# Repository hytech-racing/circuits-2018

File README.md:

# 2018 Circuits

## Getting Started with this git repository
1. Download and install [Github Desktop](https://desktop.github.com/) (basic) or [git](https://git-scm.com/book/en/v2/Getting-Started-Installing-Git) (advanced)
    * If you are using Github Desktop for the first time, be sure to read the [User Guide](https://help.github.com/desktop/guides/)
    * If you are using git for the first time, you should start off by reading a tutorial. There are many available online:
        * [Atlassian Git Tutorial](https://www.atlassian.com/git/tutorials/)
        * [Pro Git book](https://git-scm.com/book/en/v2)
    * You may want to keep a copy of [Github's Git Cheat Sheet](https://services.github.com/kit/downloads/github-git-cheat-sheet.pdf) as a reference
2. Create a Github account if you don't already have one
3. Talk to your subteam lead to be added to your respective team on the Github organization
4. Clone this repository to your computer
    * SSH: git@github.com:hytech-racing/circuits-2018.git
    * HTTPS: https://github.com/hytech-racing/circuits-2018.git

## Getting Started with EAGLE
1. Download and install [EAGLE](https://www.autodesk.com/products/eagle/overview)
2. Get the free [Educational License](https://www.autodesk.com/education/free-software/eagle) (a .edu email address is required)

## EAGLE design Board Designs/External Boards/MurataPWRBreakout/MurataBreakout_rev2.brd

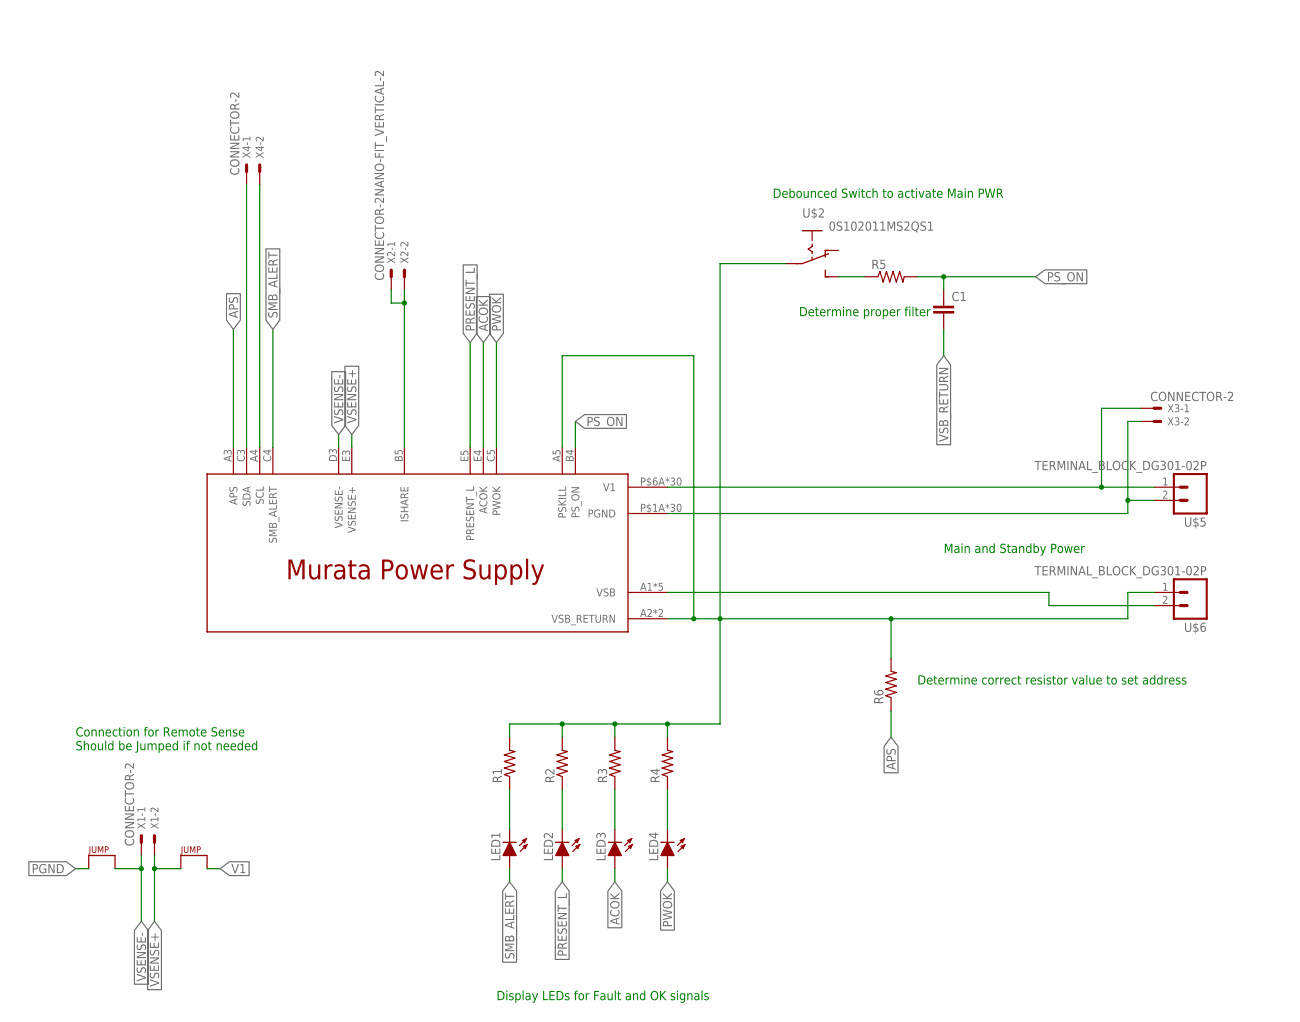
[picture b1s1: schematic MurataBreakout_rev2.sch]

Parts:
C1: CAP0805; 0805
LED1, LED2, LED3, LED4: LED-0805; LED-805
R1, R2, R3, R4, R5, R6: RESISTOR0805-RES; 0805
U$1: MURATA_POWER_SUPPLY; MURATA_POWER_SUPPLY_CONNECTOR
U$2: 0S102011MS2QS1
U$3, U$4: JUMPER.1; 1X02
U$5, U$6: TERMINAL_BLOCK_DG301-02P; DG301-02P
X1, X3, X4: CONNECTOR-2; MINIFIT_5566-2
X2: CONNECTOR-2NANO-FIT_VERTICAL-2; NANO-FIT_VERTICAL-2

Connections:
ACOK: LED3.A, U$1.E4 (ACOK)
APS: R6.1, U$1.A3 (APS)
unnamed: LED4.C, R4.1
unnamed: LED3.C, R3.1
unnamed: LED2.C, R2.1
unnamed: LED1.C, R1.1
unnamed: U$1.B5 (ISHARE), X2.P$1, X2.P$2
unnamed: R5.1, U$2.P$3 (S)
unnamed: U$1.A1 (VSB), U$1.B1 (VSB), U$1.C1 (VSB), U$1.D1 (VSB), U$1.E1 (VSB), U$6.2
PGND: U$1.P$1A (PGND), U$1.P$1B (PGND), U$1.P$1C (PGND), U$1.P$1D (PGND), U$1.P$1E (PGND), U$1.P$1F (PGND), U$1.P$2A (PGND), U$1.P$2B (PGND), U$1.P$2C (PGND), U$1.P$2D (PGND), U$1.P$2E (PGND), U$1.P$2F (PGND), U$1.P$3A (PGND), U$1.P$3B (PGND), U$1.P$3C (PGND), U$1.P$3D (PGND), U$1.P$3E (PGND), U$1.P$3F (PGND), U$1.P$4A (PGND), U$1.P$4B (PGND), U$1.P$4C (PGND), U$1.P$4D (PGND), U$1.P$4E (PGND), U$1.P$4F (PGND), U$1.P$5A (PGND), U$1.P$5B (PGND), U$1.P$5C (PGND), U$1.P$5D (PGND), U$1.P$5E (PGND), U$1.P$5F (PGND), U$4.1, U$5.2, X3.2
PRESENT_L: LED2.A, U$1.E5 (PRESENT_L)
PS_ON: C1.1, R5.2, U$1.B4 (PS_ON)
PWOK: LED4.A, U$1.C5 (PWOK)
SCL: U$1.A4 (SCL), X4.2
SDA: U$1.C3 (SDA), X4.1
SMB_ALERT: LED1.A, U$1.C4 (SMB_ALERT)
V1: U$1.P$6A (V1), U$1.P$6B (V1), U$1.P$6C (V1), U$1.P$6D (V1), U$1.P$6E (V1), U$1.P$6F (V1), U$1.P$7A (V1), U$1.P$7B (V1), U$1.P$7C (V1), U$1.P$7D (V1), U$1.P$7E (V1), U$1.P$7F (V1), U$1.P$8A (V1), U$1.P$8B (V1), U$1.P$8C (V1), U$1.P$8D (V1), U$1.P$8E (V1), U$1.P$8F (V1), U$1.P$9A (V1), U$1.P$9B (V1), U$1.P$9C (V1), U$1.P$9D (V1), U$1.P$9E (V1), U$1.P$9F (V1), U$1.P$10A (V1), U$1.P$10B (V1), U$1.P$10C (V1), U$1.P$10D (V1), U$1.P$10E (V1), U$1.P$10F (V1), U$3.2, U$5.1, X3.1
VSB_RETURN: C1.2, R1.2, R2.2, R3.2, R4.2, R6.2, U$1.A2 (VSB_RETURN), U$1.A5 (PSKILL), U$1.B2 (VSB_RETURN), U$2.P$2, U$6.1
VSENSE+: U$1.E3 (VSENSE+), U$3.1, X1.2
VSENSE-: U$1.D3 (VSENSE-), U$4.2, X1.1

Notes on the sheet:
Connection for Remote Sense Should be Jumped if not needed
Display LEDs for Fault and OK signals
Main and Standby Power
Debounced Switch to activate Main PWR
Determine correct resistor value to set address
Determine proper filter

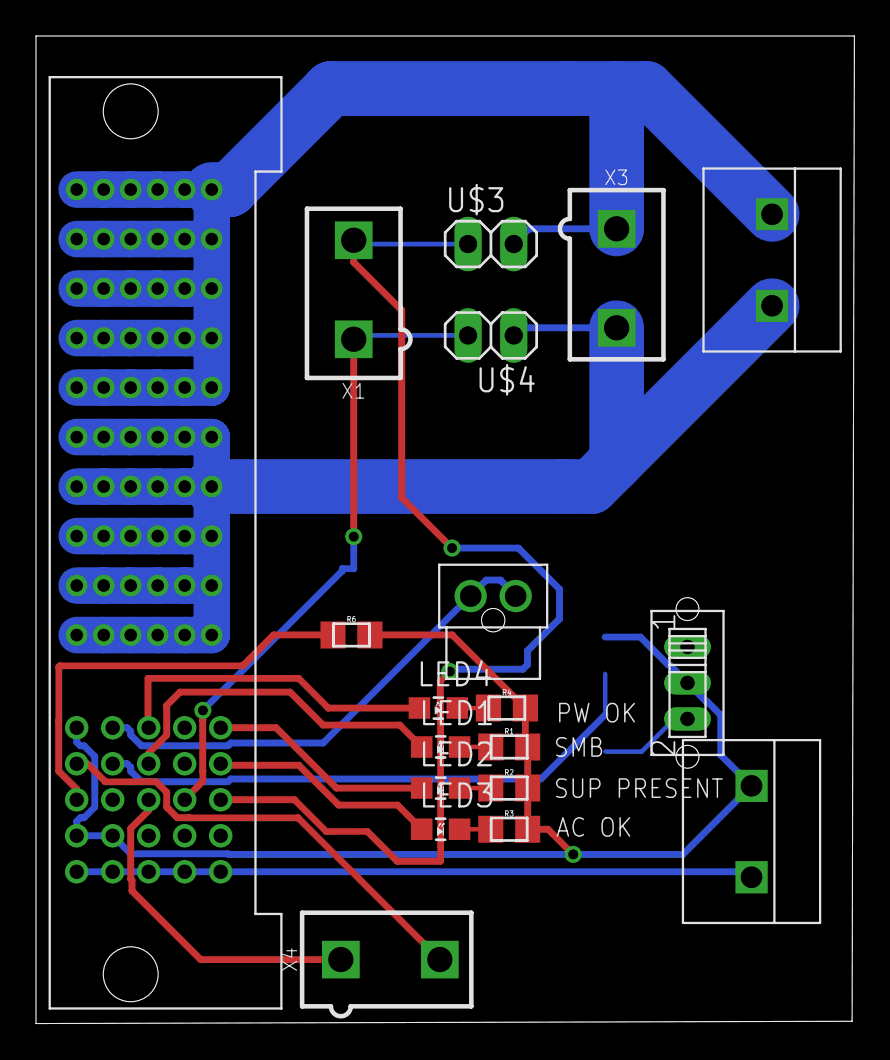
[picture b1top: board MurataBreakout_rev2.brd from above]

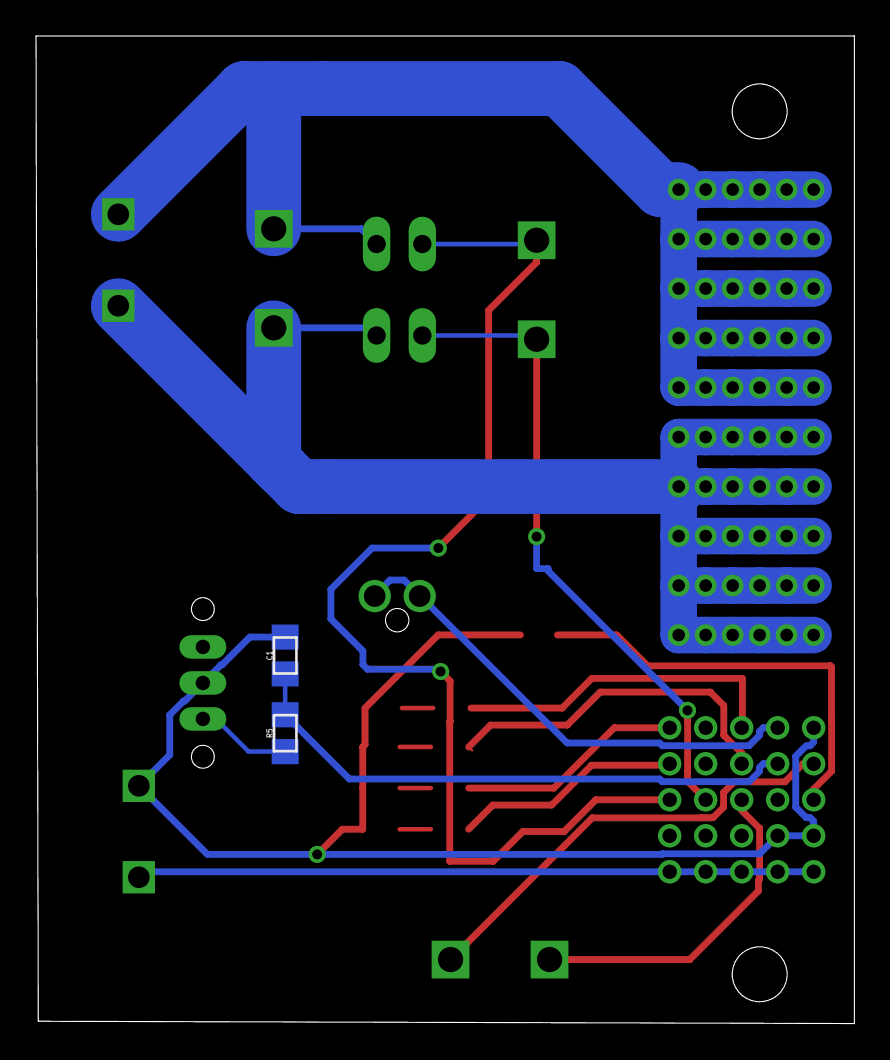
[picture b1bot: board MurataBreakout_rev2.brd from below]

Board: 2 copper layers, 45.5 x 54.9 mm, 21 parts (2 on the bottom side), 20 nets.

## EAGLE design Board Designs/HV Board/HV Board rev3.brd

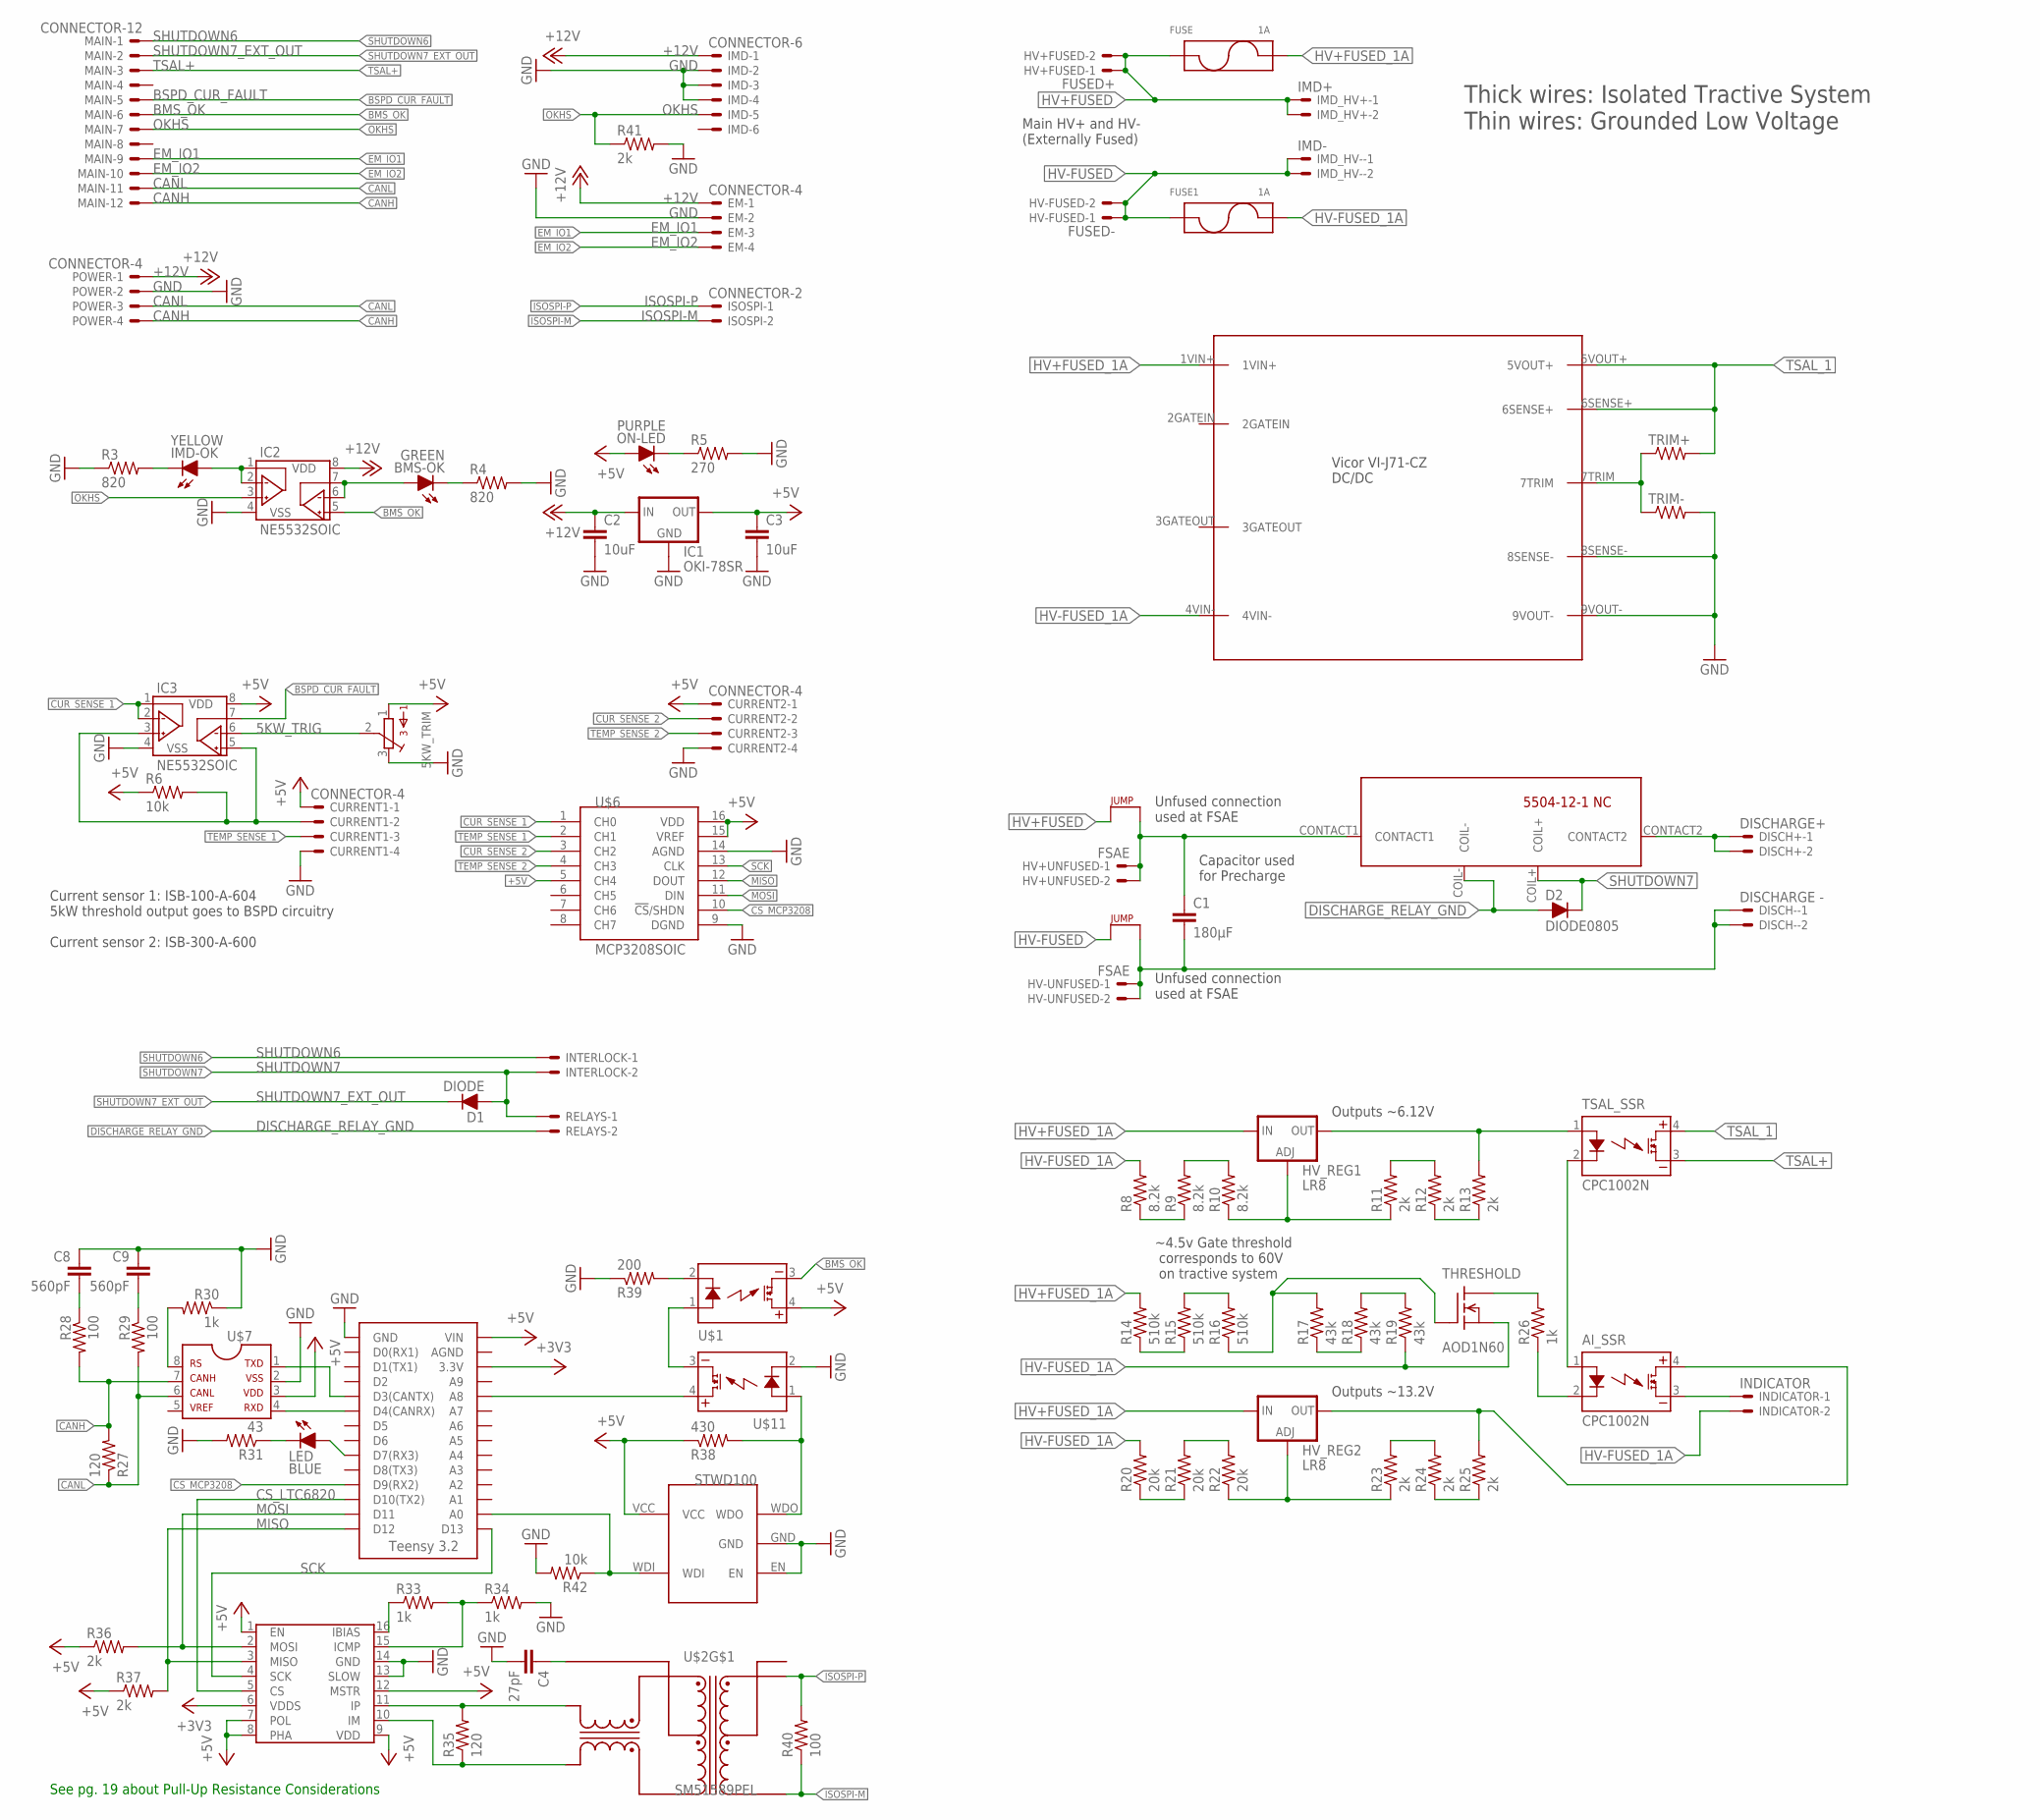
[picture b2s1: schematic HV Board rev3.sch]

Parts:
5KW_TRIM: TRIMPOT_3296C; TRIMPOT_3296
AI_SSR: CPC1002N; SOP04
BMS-OK: GREEN; LED-805
C1: 180µF; LLS2V221MELZ
C2, C3: 10uF; 0805
C4: 27pF; 0805
C8, C9: 560pF; 0805
CURRENT1, CURRENT2: CONNECTOR-4; MINIFIT_5566-4
D1: DIODE; DO-41
D2: DIODE0805; 0805_D
DISCH+: DISCHARGE+; MINIFIT_5566-2
DISCH-: DISCHARGE -; MINIFIT_5566-2
EM: CONNECTOR-4; NANO-FIT_VERTICAL-4
FUSE, FUSE1: 1A; 0751.0110
HV+FUSED: FUSED+; MINIFIT_5566-2
HV+UNFUSED: FSAE; MINIFIT_5566-2
HV-FUSED: FUSED-; MINIFIT_5566-2
HV-UNFUSED: FSAE; MINIFIT_5566-2
HV_REG1, HV_REG2: LR8; TO-252
IC1: OKI-78SR
IC2, IC3: NE5532SOIC; SOIC-08
IMD: CONNECTOR-6; NANO-FIT_VERTICAL-6
IMD-OK: YELLOW; LED-805
IMD_HV+: IMD+; MINIFIT_5566-2
IMD_HV-: IMD-; MINIFIT_5566-2
INDICATOR: INDICATOR; MINIFIT_5566-2
INTERLOCK: MINIFIT_5566-2
ISOSPI: CONNECTOR-2; NANO-FIT_VERTICAL-2
LED: BLUE; LED-805
MAIN: CONNECTOR-12; MINIFIT_5566-12
ON-LED: PURPLE; LED-805
POWER: CONNECTOR-4; MINIFIT_5566-4
R3, R4: 820; 0805
R5: 270; 0805
R6, R42: 10k; 0805
R8, R9, R10: 8.2k; 0805
R11, R12, R13, R23, R24, R25, R36, R37, R41: 2k; 0805
R14, R15, R16: 510k; 0805
R17, R18, R19: 43k; 0805
R20, R21, R22: 20k; 0805
R26, R30, R33, R34: 1k; 0805
R27, R35: 120; 0805
R28, R29, R40: 100; 0805
R31: 43; 0805
R38: 430; 0805
R39: 200; 0805
RELAYS: MINIFIT_5566-2
THRESHOLD: AOD1N60; TO-252
TRIM+: RESISTOR0805-RES; 0805
TRIM-: RESISTOR0805-RES; 0805
TSAL_SSR: CPC1002N; SOP04
U$1, U$11: CPC1002N; SOP04
U$2: SM51589PEL
U$3, U$4: JUMPER.3; AXIAL-0.3
U$5: HV_DCDC_VI-J71-CZ
U$6: MCP3208SOIC; SOIC-16
U$7: MCP2551; SOIC-08
U$8: LTC6820; MSOP-16
U$9: TEENSY_3.2_SIMPLE
U$10: STWD100; SOT23-5
U$12: 5504-12-1-NC

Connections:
5KW_TRIG: 5KW_TRIM.2, IC3.6 (VINB-)
+3V3: U$8.6 (VDDS), U$9.3.3V
+5V: 5KW_TRIM.1, C3.1, CURRENT1.1, CURRENT2.1, IC1.3 (OUT), IC3.8 (VDD), ON-LED.A, R6.1, R36.1, R37.1, R38.1, U$1.4 (DC+), U$6.5 (CH4), U$6.15 (VREF), U$6.16 (VDD), U$7.3, U$8.1 (EN), U$8.7 (POL), U$8.8 (PHA), U$8.9 (VDD), U$8.12 (MSTR), U$9.VIN, U$10.VCC
+12V: C2.1, EM.P$1, IC1.1 (IN), IC2.8 (VDD), IMD.P$1, POWER.1
BMS_OK: IC2.5 (VINB+), MAIN.6, U$1.3 (DC-)
BMS_WATCH: U$1.1 (CONTROL+), U$11.3 (DC-)
BSPD_CUR_FAULT: IC3.7 (VOUTB), MAIN.5
CANH: MAIN.12, POWER.4, R27.2, R28.2, U$7.7
CANL: MAIN.11, POWER.3, R27.1, R29.2, U$7.6
CS_LTC6820: U$8.5 (CS), U$9.D10(TX2)
CS_MCP3208: U$6.10 (!CS!/SHDN), U$9.D9(RX2)
CUR_SENSE_1: IC3.1 (VOUTA), IC3.2 (VINA-), U$6.1 (CH0)
CUR_SENSE_1_RAW: CURRENT1.2, IC3.3 (VINA+), IC3.5 (VINB+), R6.2
CUR_SENSE_2: CURRENT2.2, U$6.3 (CH2)
DISCHARGE_RELAY_GND: D2.A, RELAYS.2, U$12.COIL-
EM_IO1: EM.P$3, MAIN.9
EM_IO2: EM.P$4, MAIN.10
GND: 5KW_TRIM.3, C2.2, C3.2, C4.2, C8.1, C9.1, CURRENT1.4, CURRENT2.4, EM.P$2, IC1.2 (GND), IC2.4 (VSS), IC3.4 (VSS), IMD.P$2, IMD.P$3, IMD.P$4, POWER.2, R3.1, R4.2, R5.2, R30.1, R31.2, R34.2, R39.1, R41.2, R42.2, TRIM-.2, U$5.8SENSE-, U$5.9VOUT-, U$6.9 (DGND), U$6.14 (AGND), U$7.2, U$8.13 (SLOW), U$8.14 (GND), U$9.GND, U$10.EN, U$10.GND, U$11.2 (CONTROL-)
HV+FUSED: FUSE.L1 (P1), FUSE.L2 (P1), HV+FUSED.1, HV+FUSED.2, IMD_HV+.1, IMD_HV+.2, U$3.P$1
HV+FUSED_1A: FUSE.R1 (P2), FUSE.R2 (P2), HV_REG1.1 (IN), HV_REG2.1 (IN), R14.2, U$5.1VIN+
HV+UNFUSED_FSAE: C1.P$1 (1), HV+UNFUSED.1, HV+UNFUSED.2, U$3.P$2, U$12.CONTACT1
HV+UNFUSED_FSAE_DISCHARGE: DISCH+.1, DISCH+.2, U$12.CONTACT2
HV-FUSED: FUSE1.L1 (P1), FUSE1.L2 (P1), HV-FUSED.1, HV-FUSED.2, IMD_HV-.1, IMD_HV-.2, U$4.P$1
HV-FUSED_1A: FUSE1.R1 (P2), FUSE1.R2 (P2), INDICATOR.2, R8.2, R19.1, R20.2, THRESHOLD.3 (S), U$5.4VIN-
HV-UNFUSED_FSAE: C1.P$2 (2), DISCH-.1, DISCH-.2, HV-UNFUSED.1, HV-UNFUSED.2, U$4.P$2
ISOSPI-M: ISOSPI.P$2, R40.1, U$2.3 (MX-)
ISOSPI-P: ISOSPI.P$1, R40.2, U$2.2 (MX+)
MISO: R37.2, U$6.12 (DOUT), U$8.3 (MISO), U$9.D12
MOSI: R36.2, U$6.11 (DIN), U$8.2 (MOSI), U$9.D11
unnamed: AI_SSR.4 (DC+), HV_REG2.2(TAB) (OUT), R25.2
unnamed: HV_REG1.2(TAB) (OUT), R13.2, TSAL_SSR.1 (CONTROL+)
unnamed: ON-LED.C, R5.1
unnamed: R39.2, U$1.2 (CONTROL-)
unnamed: AI_SSR.2 (CONTROL-), R26.1
unnamed: AI_SSR.1 (CONTROL+), TSAL_SSR.2 (CONTROL-)
unnamed: AI_SSR.3 (DC-), INDICATOR.1
unnamed: R8.1, R9.1
unnamed: R26.2, THRESHOLD.2(TAB) (D)
unnamed: R14.1, R15.1
unnamed: R15.2, R16.2
unnamed: R17.1, R18.1
unnamed: R18.2, R19.2
unnamed: R9.2, R10.2
unnamed: HV_REG2.3 (ADJ), R22.1, R23.1
unnamed: R11.2, R12.2
unnamed: R12.1, R13.1
unnamed: HV_REG1.3 (ADJ), R10.1, R11.1
unnamed: R23.2, R24.2
unnamed: R24.1, R25.1
unnamed: R21.2, R22.2
unnamed: R16.1, R17.2, THRESHOLD.1 (G)
unnamed: R20.1, R21.1
unnamed: U$7.1, U$9.D3(CANTX)
unnamed: R30.2, U$7.8
unnamed: C8.2, R28.1
unnamed: C9.2, R29.1
unnamed: LED.C, R31.1
unnamed: R33.1, U$8.16 (IBIAS)
unnamed: R33.2, R34.1, U$8.15 (ICMP)
unnamed: R35.1, U$2.22 (TD-), U$8.10 (IM)
unnamed: R35.2, U$2.23 (TD+), U$8.11 (IP)
unnamed: C4.1, U$2.24 (TCT)
unnamed: U$7.4, U$9.D4(CANRX)
unnamed: LED.A, U$9.D7(RX3)
unnamed: R38.2, U$10.WDO, U$11.1 (CONTROL+)
unnamed: U$9.A8, U$11.4 (DC+)
unnamed: IC2.1 (VOUTA), IC2.2 (VINA-), IMD-OK.A
unnamed: BMS-OK.A, IC2.6 (VINB-), IC2.7 (VOUTB)
unnamed: BMS-OK.C, R4.1
unnamed: IMD-OK.C, R3.2
unnamed: R42.1, U$9.A0, U$10.WDI
OKHS: IC2.3 (VINA+), IMD.P$5, MAIN.7, R41.1
SCK: U$6.13 (CLK), U$8.4 (SCK), U$9.D13
SHUTDOWN6: INTERLOCK.1, MAIN.1
SHUTDOWN7: D1.A, D2.C, INTERLOCK.2, RELAYS.1, U$12.COIL+
SHUTDOWN7_EXT_OUT: D1.C, MAIN.2
TEMP_SENSE_1: CURRENT1.3, U$6.2 (CH1)
TEMP_SENSE_2: CURRENT2.3, U$6.4 (CH3)
TRIM: TRIM+.1, TRIM-.1, U$5.7TRIM
TSAL+: MAIN.3, TSAL_SSR.3 (DC-)
TSAL_1: TRIM+.2, TSAL_SSR.4 (DC+), U$5.5VOUT+, U$5.6SENSE+

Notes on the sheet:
Current sensor 1: ISB-100-A-604 5kW threshold output goes to BSPD circuitry Current sensor 2: ISB-300-A-600
Unfused connection used at FSAE
Main HV+ and HV- (Externally Fused)
~4.5v Gate threshold corresponds to 60V on tractive system
Thick wires: Isolated Tractive System Thin wires: Grounded Low Voltage
Outputs ~6.12V
Outputs ~13.2V
See pg. 19 about Pull-Up Resistance Considerations
Capacitor used for Precharge

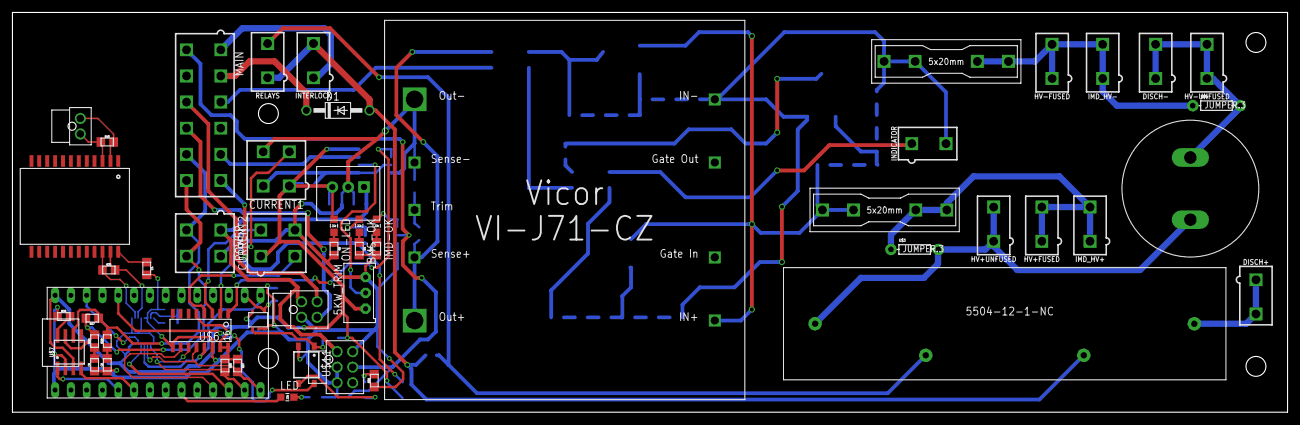
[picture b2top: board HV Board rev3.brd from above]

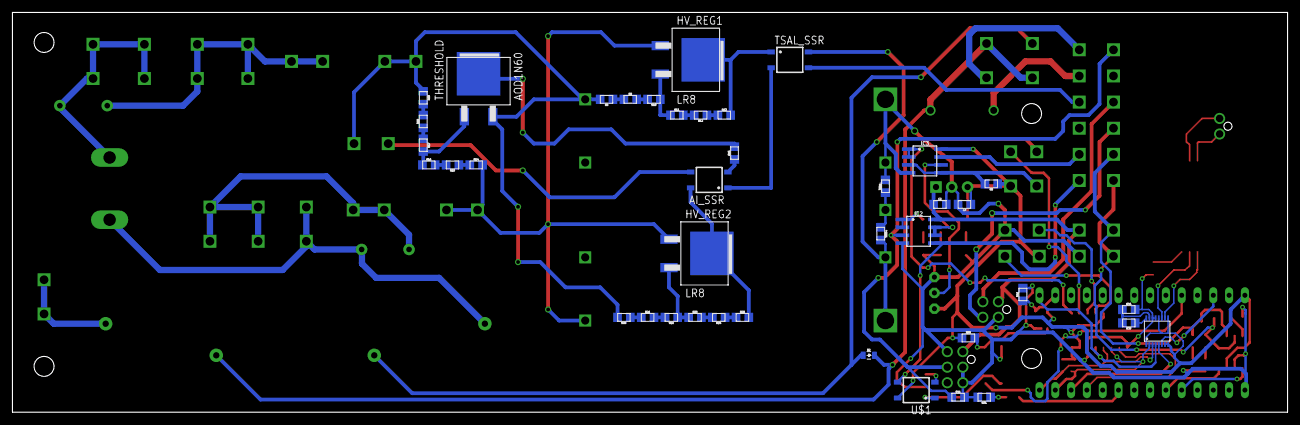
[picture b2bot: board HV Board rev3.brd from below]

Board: 2 copper layers, 205.0 x 64.3 mm, 93 parts (40 on the bottom side), 81 nets.

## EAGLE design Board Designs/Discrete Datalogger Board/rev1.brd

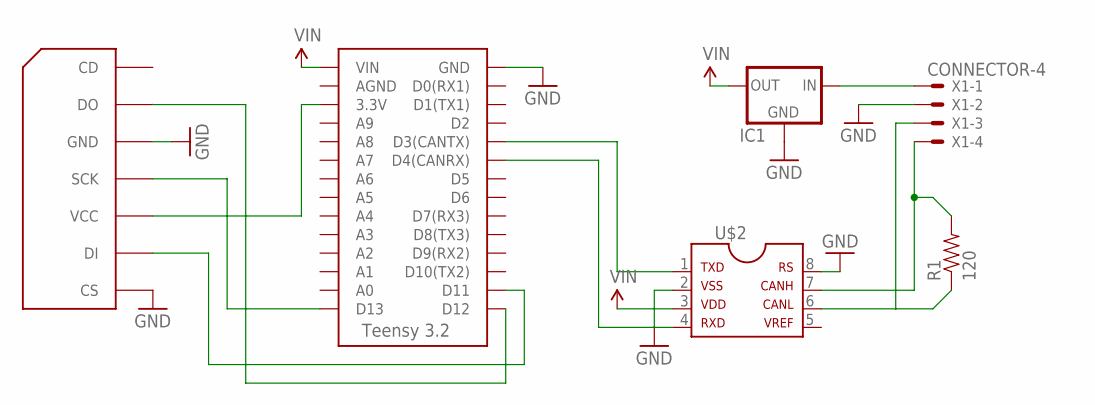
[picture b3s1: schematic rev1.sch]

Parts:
IC1: 5VREG_L7805_VERT; TO-220
R1: 120; AXIAL-0.3
U$1: TEENSY_3.2_SIMPLE
U$2: MCP2551DIL; DIL08
U$3: SDCARD_INTERFACE
X1: CONNECTOR-4; MINIFIT_5566-4

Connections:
GND: IC1.2 (GND), U$1.GND, U$2.2, U$2.8, U$3.CS, U$3.GND, X1.2
unnamed: IC1.1 (IN), X1.1
unnamed: R1.P$2 (2), U$2.7, X1.4
unnamed: R1.P$1 (1), U$2.6, X1.3
unnamed: U$1.D3(CANTX), U$2.1
unnamed: U$1.D4(CANRX), U$2.4
unnamed: U$1.D13, U$3.SCK
unnamed: U$1.D11, U$3.DI
unnamed: U$1.3.3V, U$3.VCC
unnamed: U$1.D12, U$3.DO
VIN: IC1.3 (OUT), U$1.VIN, U$2.3

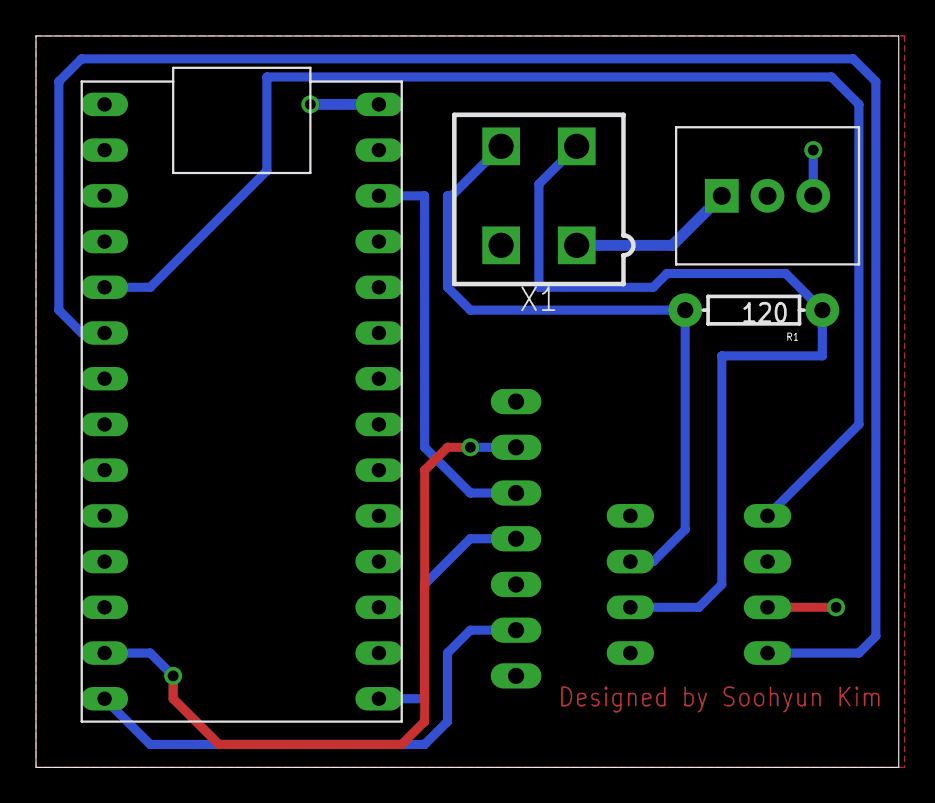
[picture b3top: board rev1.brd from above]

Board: 2 copper layers, 47.9 x 40.6 mm, 6 parts (1 on the bottom side), 11 nets.

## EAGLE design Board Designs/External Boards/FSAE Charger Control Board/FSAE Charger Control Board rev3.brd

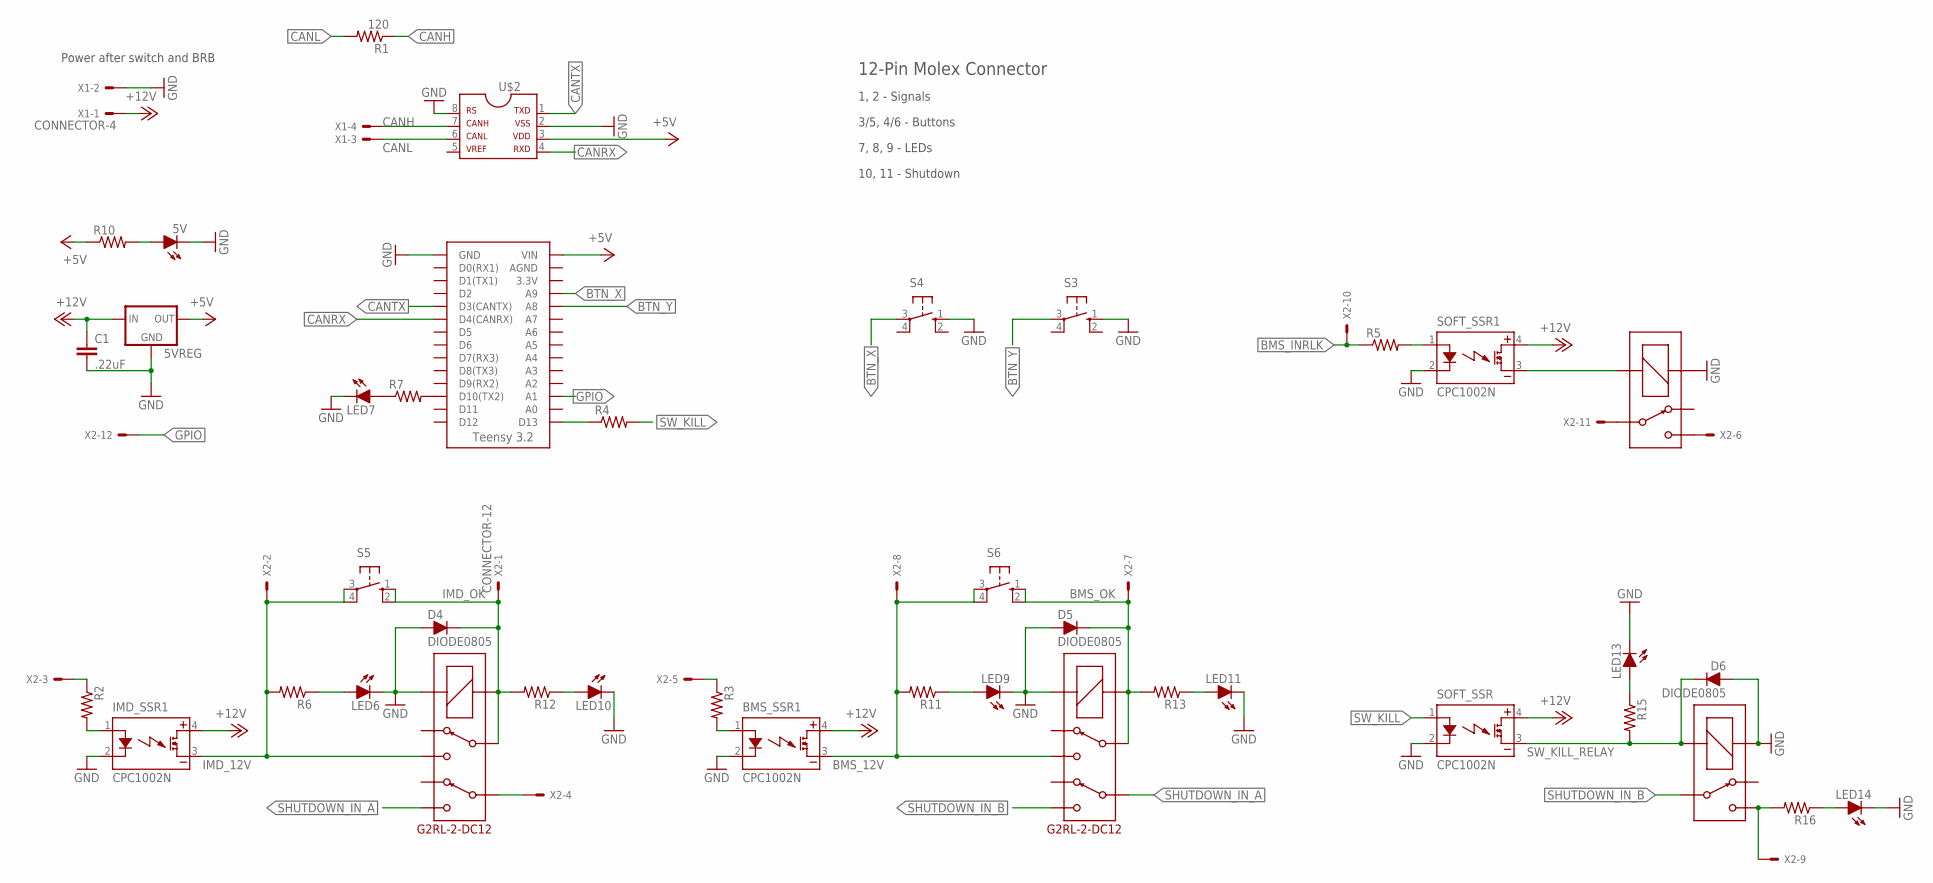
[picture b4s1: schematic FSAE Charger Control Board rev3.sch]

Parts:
5V: LED-0805; LED-805
5VREG: 5VREG_LM340-NLM340MPX-5.0/NOPB; SOT223
BMS_SSR1: CPC1002N; SOP04
C1: .22uF; 0805
D4, D5, D6: DIODE0805; 0805_D
IMD_SSR1: CPC1002N; SOP04
LED6, LED7, LED9, LED10, LED11, LED13, LED14: LED-0805; LED-805
R1: 120; 0805
R2, R3, R4, R5, R6, R7, R10, R11, R12, R13, R15, R16: RESISTOR0805-RES; 0805
S3, S4, S5, S6: BTN_10-XX; B3F-10XX
SOFT_SSR, SOFT_SSR1: CPC1002N; SOP04
U$1: TEENSY_3.2_SIMPLE
U$2: MCP2551; SOIC-08
U$3, U$8: G5LE; ZF112
U$6, U$7: G2RL-2-DC12; G2RL-2
X1: CONNECTOR-4; MINIFIT_5566-4
X2: CONNECTOR-12; MINIFIT_5566-12

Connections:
+5V: 5VREG.3 (OUT), R10.1, U$1.VIN, U$2.3
+12V: 5VREG.1 (IN), BMS_SSR1.4 (DC+), C1.1, IMD_SSR1.4 (DC+), SOFT_SSR.4 (DC+), SOFT_SSR1.4 (DC+), X1.1
BMS_12V: BMS_SSR1.3 (DC-), R11.2, S6.3, S6.4 (P1), U$7.4, X2.8
BMS_INRLK: R5.1, X2.10
BMS_OK: D5.C, R13.2, S6.1 (S), S6.2 (S1), U$7.3, U$7.COIL-, X2.7
BTN_X: S4.3, U$1.A9
BTN_Y: S3.3, U$1.A8
CANH: R1.1, U$2.7, X1.4
CANL: R1.2, U$2.6, X1.3
CANRX: U$1.D4(CANRX), U$2.4
CANTX: U$1.D3(CANTX), U$2.1
GND: 5V.C, 5VREG.2 (GND), 5VREG.4 (GND), BMS_SSR1.2 (CONTROL-), C1.2, D4.A, D5.A, D6.A, IMD_SSR1.2 (CONTROL-), LED6.C, LED7.C, LED9.C, LED10.C, LED11.C, LED13.C, LED14.C, S3.1 (S), S4.1 (S), SOFT_SSR.2 (CONTROL-), SOFT_SSR1.2 (CONTROL-), U$1.GND, U$2.2, U$2.8, U$3.1 (COIL+), U$6.COIL+, U$7.COIL+, U$8.1 (COIL+), X1.2
GPIO: U$1.A1, X2.12
IMD_12V: IMD_SSR1.3 (DC-), R6.2, S5.3, S5.4 (P1), U$6.4, X2.2
IMD_OK: D4.C, R12.2, S5.1 (S), S5.2 (S1), U$6.3, U$6.COIL-, X2.1
unnamed: SOFT_SSR1.3 (DC-), U$3.2 (COIL-)
unnamed: LED7.A, R7.1
unnamed: 5V.A, R10.2
unnamed: IMD_SSR1.1 (CONTROL+), R2.2
unnamed: U$3.S, X2.6
unnamed: LED6.A, R6.1
unnamed: LED9.A, R11.1
unnamed: LED10.A, R12.1
unnamed: U$3.P, X2.11
unnamed: R7.2, U$1.D10(TX2)
unnamed: BMS_SSR1.1 (CONTROL+), R3.2
unnamed: LED11.A, R13.1
unnamed: LED14.A, R16.1
unnamed: LED13.A, R15.1
unnamed: R2.1, X2.3
unnamed: R3.1, X2.5
unnamed: R5.2, SOFT_SSR1.1 (CONTROL+)
unnamed: R4.1, U$1.D13
SHUTDOWN_IN: U$6.6, X2.4
SHUTDOWN_IN_A: U$6.5, U$7.6
SHUTDOWN_IN_B: U$7.5, U$8.P
SHUTDOWN_OUT: R16.2, U$8.S, X2.9
SW_KILL: R4.2, SOFT_SSR.1 (CONTROL+)
SW_KILL_RELAY: D6.C, R15.2, SOFT_SSR.3 (DC-), U$8.2 (COIL-)

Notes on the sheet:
Power after switch and BRB
7, 8, 9 - LEDs
3/5, 4/6 - Buttons
1, 2 - Signals
10, 11 - Shutdown
12-Pin Molex Connector

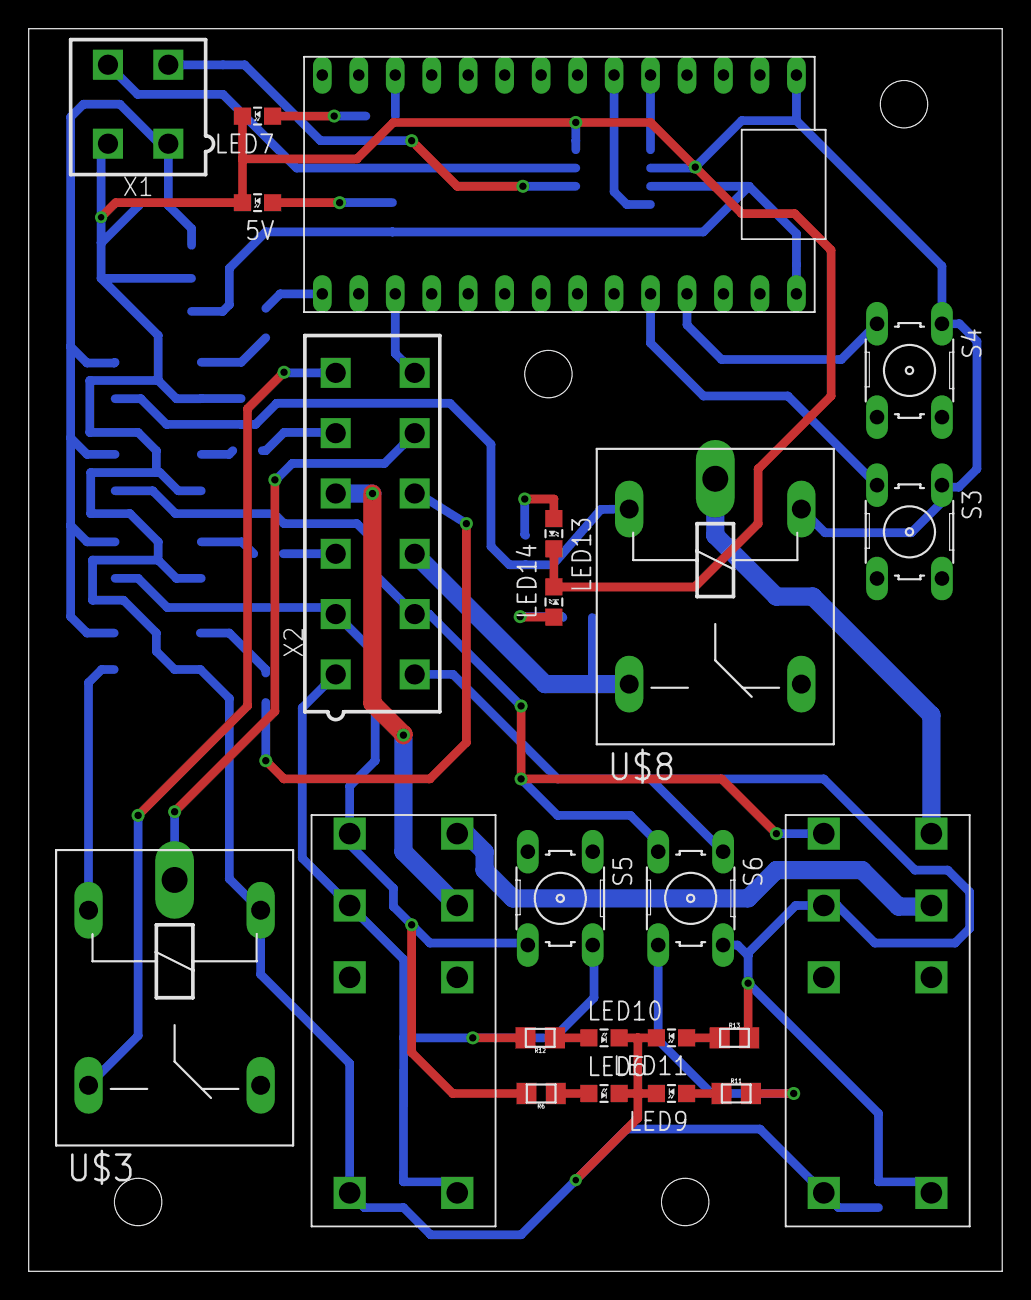
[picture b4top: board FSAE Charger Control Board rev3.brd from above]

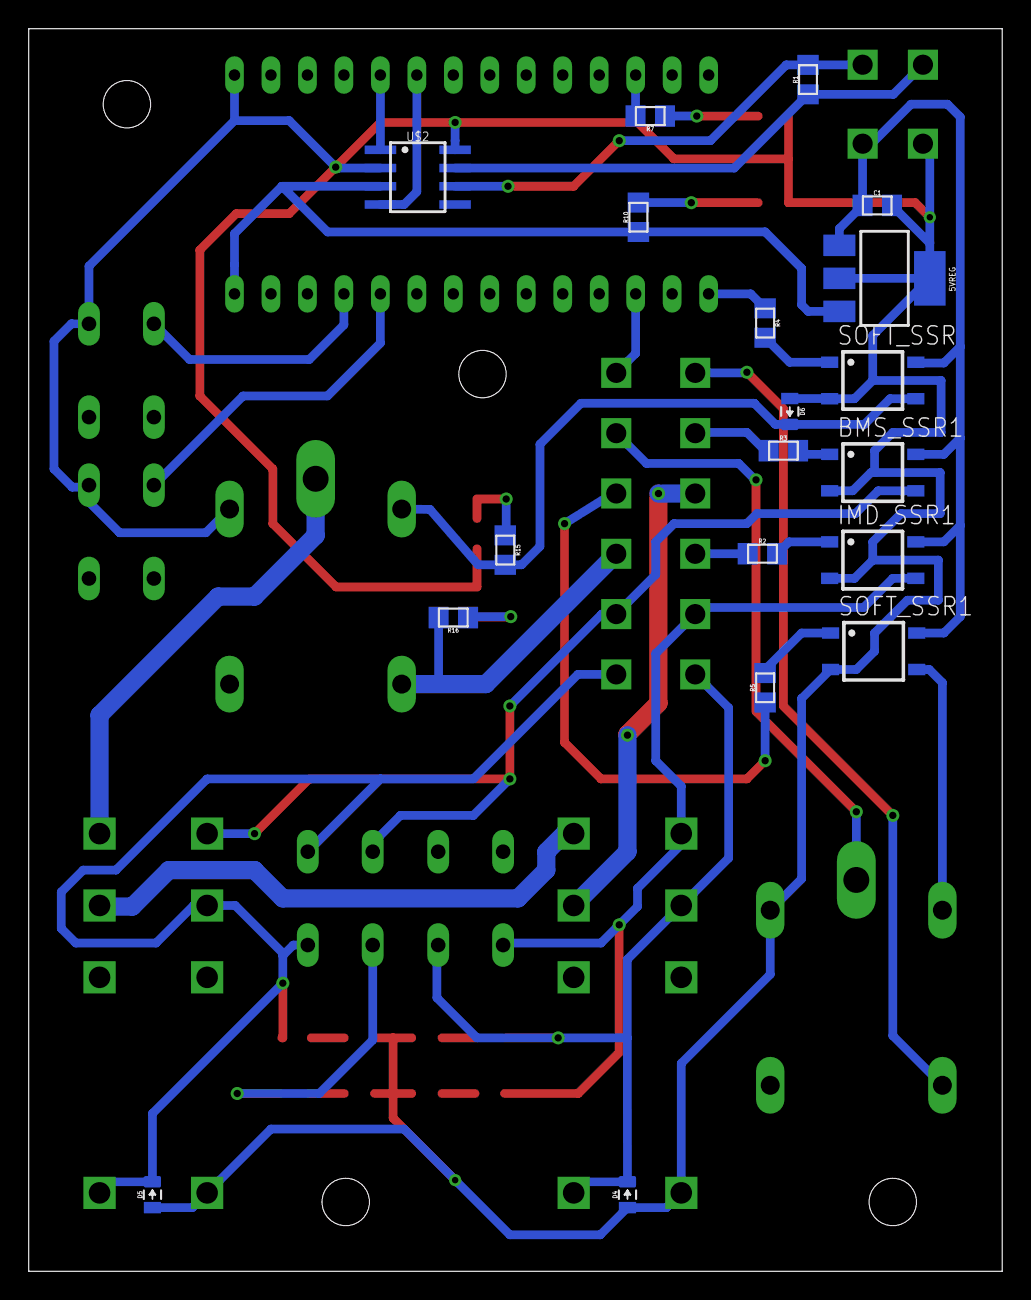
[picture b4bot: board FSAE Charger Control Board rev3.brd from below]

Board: 2 copper layers, 67.8 x 86.5 mm, 42 parts (19 on the bottom side), 39 nets.

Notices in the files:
parts and their libraries:
SparkFun-FreqCtrl: Licensing: Creative Commons ShareAlike 4.0 International - https://creativecommons.org/licenses/by-sa/4.0
